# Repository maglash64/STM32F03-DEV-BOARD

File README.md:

# STM32F03-DEV-BOARD
A 2-Layer Development and Evaluation board for STM32F03 MCU

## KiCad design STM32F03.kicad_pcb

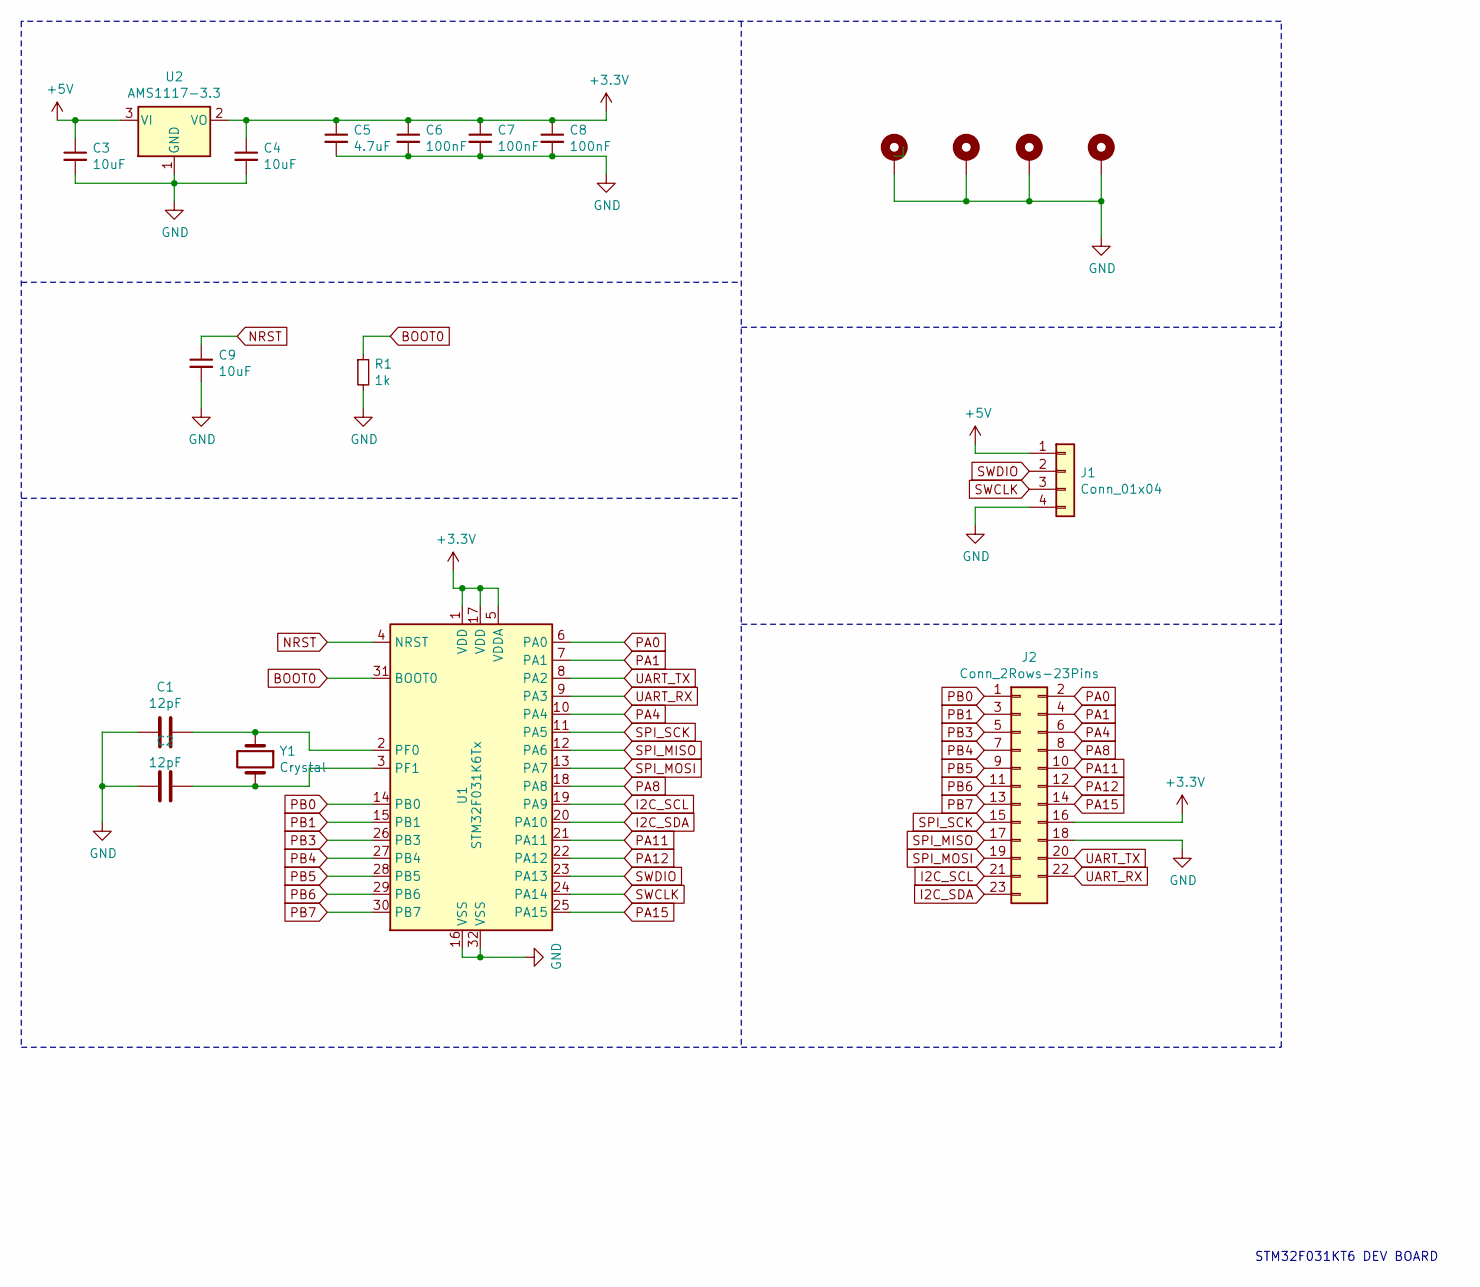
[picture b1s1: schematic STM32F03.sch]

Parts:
C1, C2: 12pF; C_1206_3216Metric
C3, C4, C9: 10uF; C_1206_3216Metric
C5: 4.7uF; C_1206_3216Metric
C6, C7, C8: 100nF; C_1206_3216Metric
H1, H2, H3, H4: MountingHole_Pad; MountingHole_3.2mm_M3_DIN965_Pad
J1: Conn_01x04; PinHeader_1x04_P2.54mm_Vertical
J2: Conn_2Rows-23Pins; PinHeader_2x12_P2.54mm_Vertical
R1: 1k; R_1206_3216Metric
U1: STM32F031K6Tx; LQFP-32_7x7mm_P0.8mm
U2: AMS1117-3.3; SOT-223-3_TabPin2
Y1: Crystal; Crystal_HC49-4H_Vertical

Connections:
+3V3: C4.1, C5.1, C6.1, C7.1, C8.1, J2.16, U1.1 (VDD), U1.5 (VDDA), U1.17 (VDD), U2.2 (VO)
+5V: C3.1, J1.1, U2.3 (VI)
BOOT0: R1.1, U1.31 (BOOT0)
GND: C1.2, C2.1, C3.2, C4.2, C5.2, C6.2, C7.2, C8.2, C9.2, H1.1, H2.1, H3.1, H4.1, J1.4, J2.18, R1.2, U1.16 (VSS), U1.32 (VSS), U2.1 (GND)
I2C_SCL: J2.21, U1.19 (PA9)
I2C_SDA: J2.23, U1.20 (PA10)
NRST: C9.1, U1.4 (NRST)
unnamed: C1.1, U1.2 (PF0), Y1.1
unnamed: C2.2, U1.3 (PF1), Y1.2
PA0: J2.2, U1.6 (PA0)
PA1: J2.4, U1.7 (PA1)
PA4: J2.6, U1.10 (PA4)
PA8: J2.8, U1.18 (PA8)
PA11: J2.10, U1.21 (PA11)
PA12: J2.12, U1.22 (PA12)
PA15: J2.14, U1.25 (PA15)
PB0: J2.1, U1.14 (PB0)
PB1: J2.3, U1.15 (PB1)
PB3: J2.5, U1.26 (PB3)
PB4: J2.7, U1.27 (PB4)
PB5: J2.9, U1.28 (PB5)
PB6: J2.11, U1.29 (PB6)
PB7: J2.13, U1.30 (PB7)
SPI_MISO: J2.17, U1.12 (PA6)
SPI_MOSI: J2.19, U1.13 (PA7)
SPI_SCK: J2.15, U1.11 (PA5)
SWCLK: J1.3, U1.24 (PA14)
SWDIO: J1.2, U1.23 (PA13)
UART_RX: J2.22, U1.9 (PA3)
UART_TX: J2.20, U1.8 (PA2)

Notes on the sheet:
STM32F031KT6 DEV BOARD

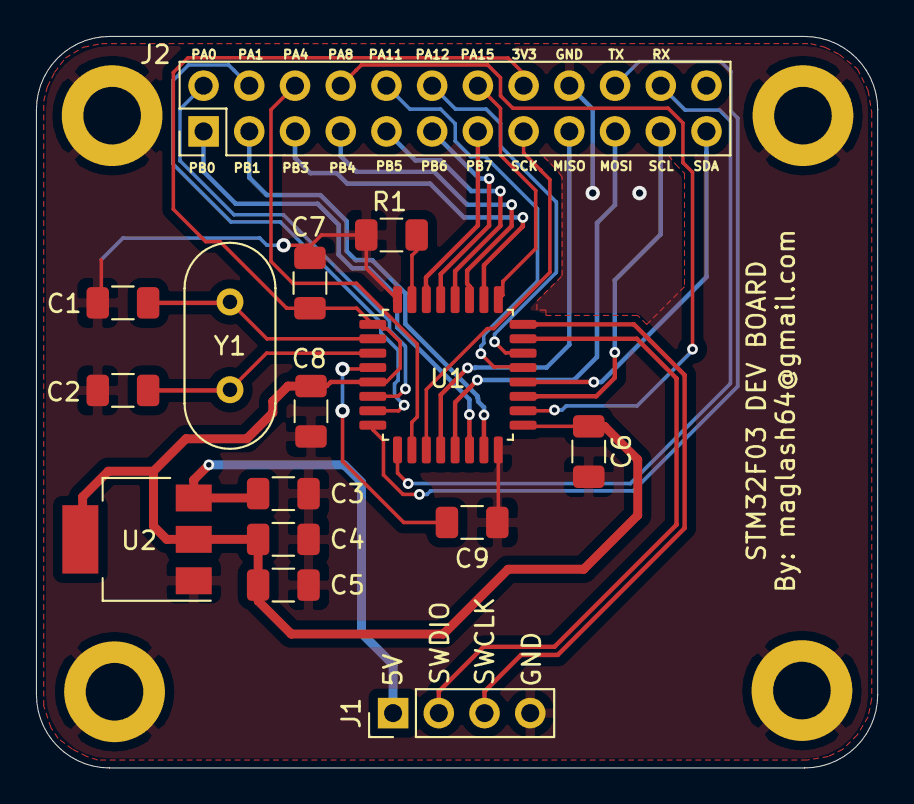
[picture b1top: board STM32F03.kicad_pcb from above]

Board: 2 copper layers, 46.7 x 40.6 mm, 19 parts (0 on the bottom side), 30 nets.

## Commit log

2020-07-04 uploaded
2020-07-04 created
